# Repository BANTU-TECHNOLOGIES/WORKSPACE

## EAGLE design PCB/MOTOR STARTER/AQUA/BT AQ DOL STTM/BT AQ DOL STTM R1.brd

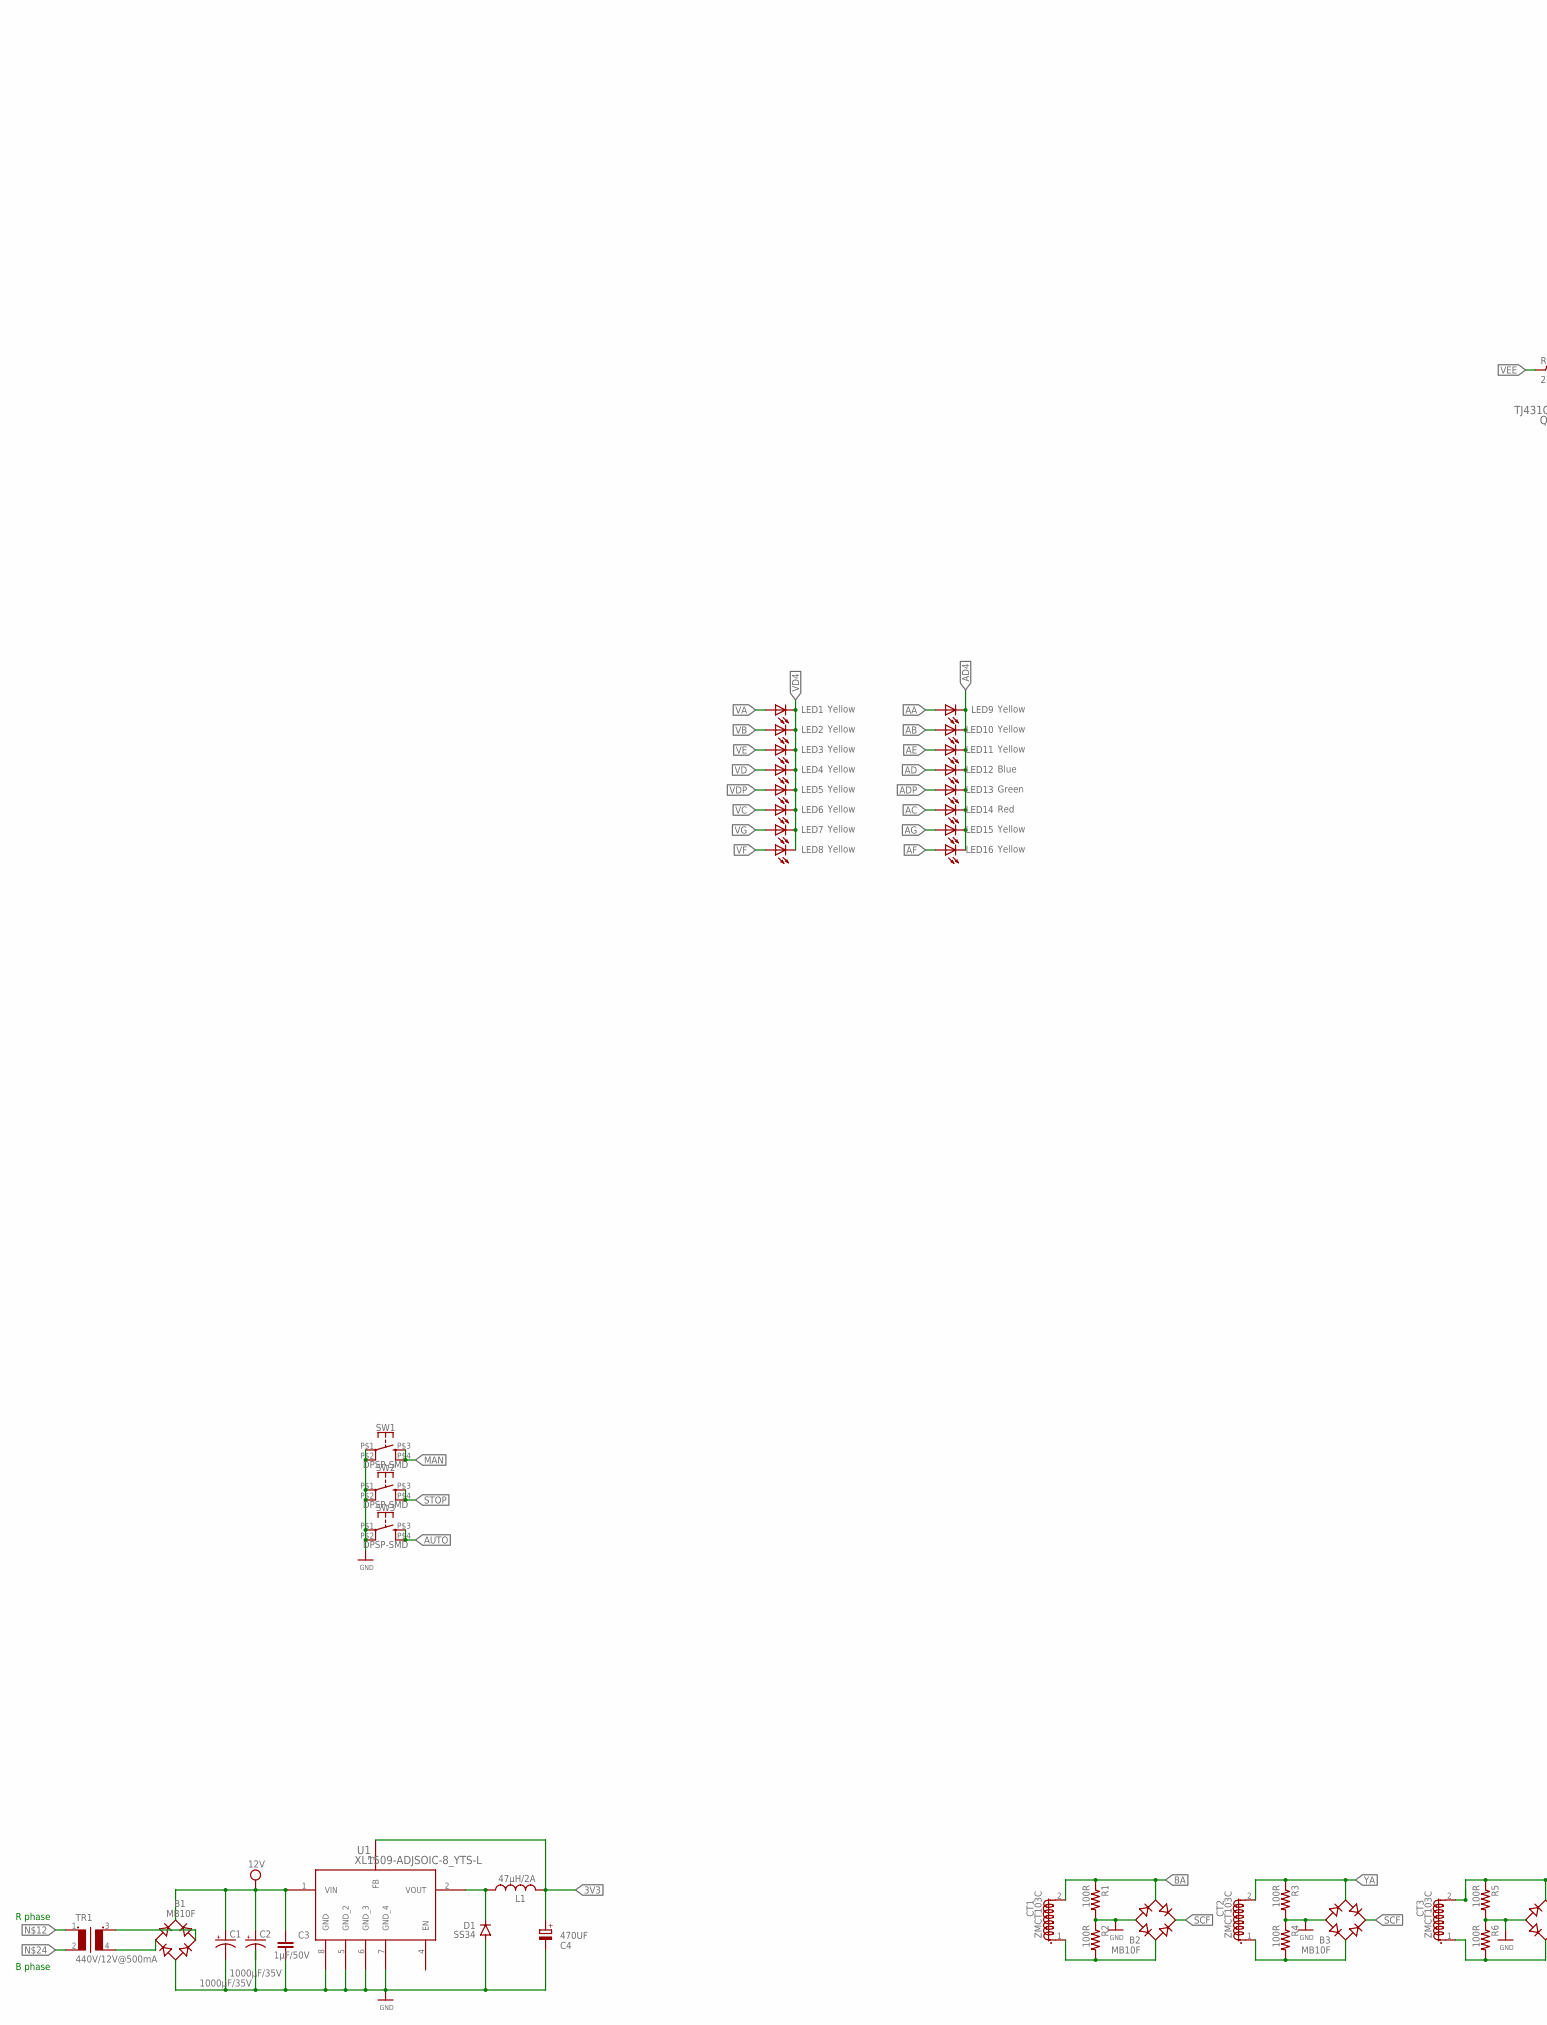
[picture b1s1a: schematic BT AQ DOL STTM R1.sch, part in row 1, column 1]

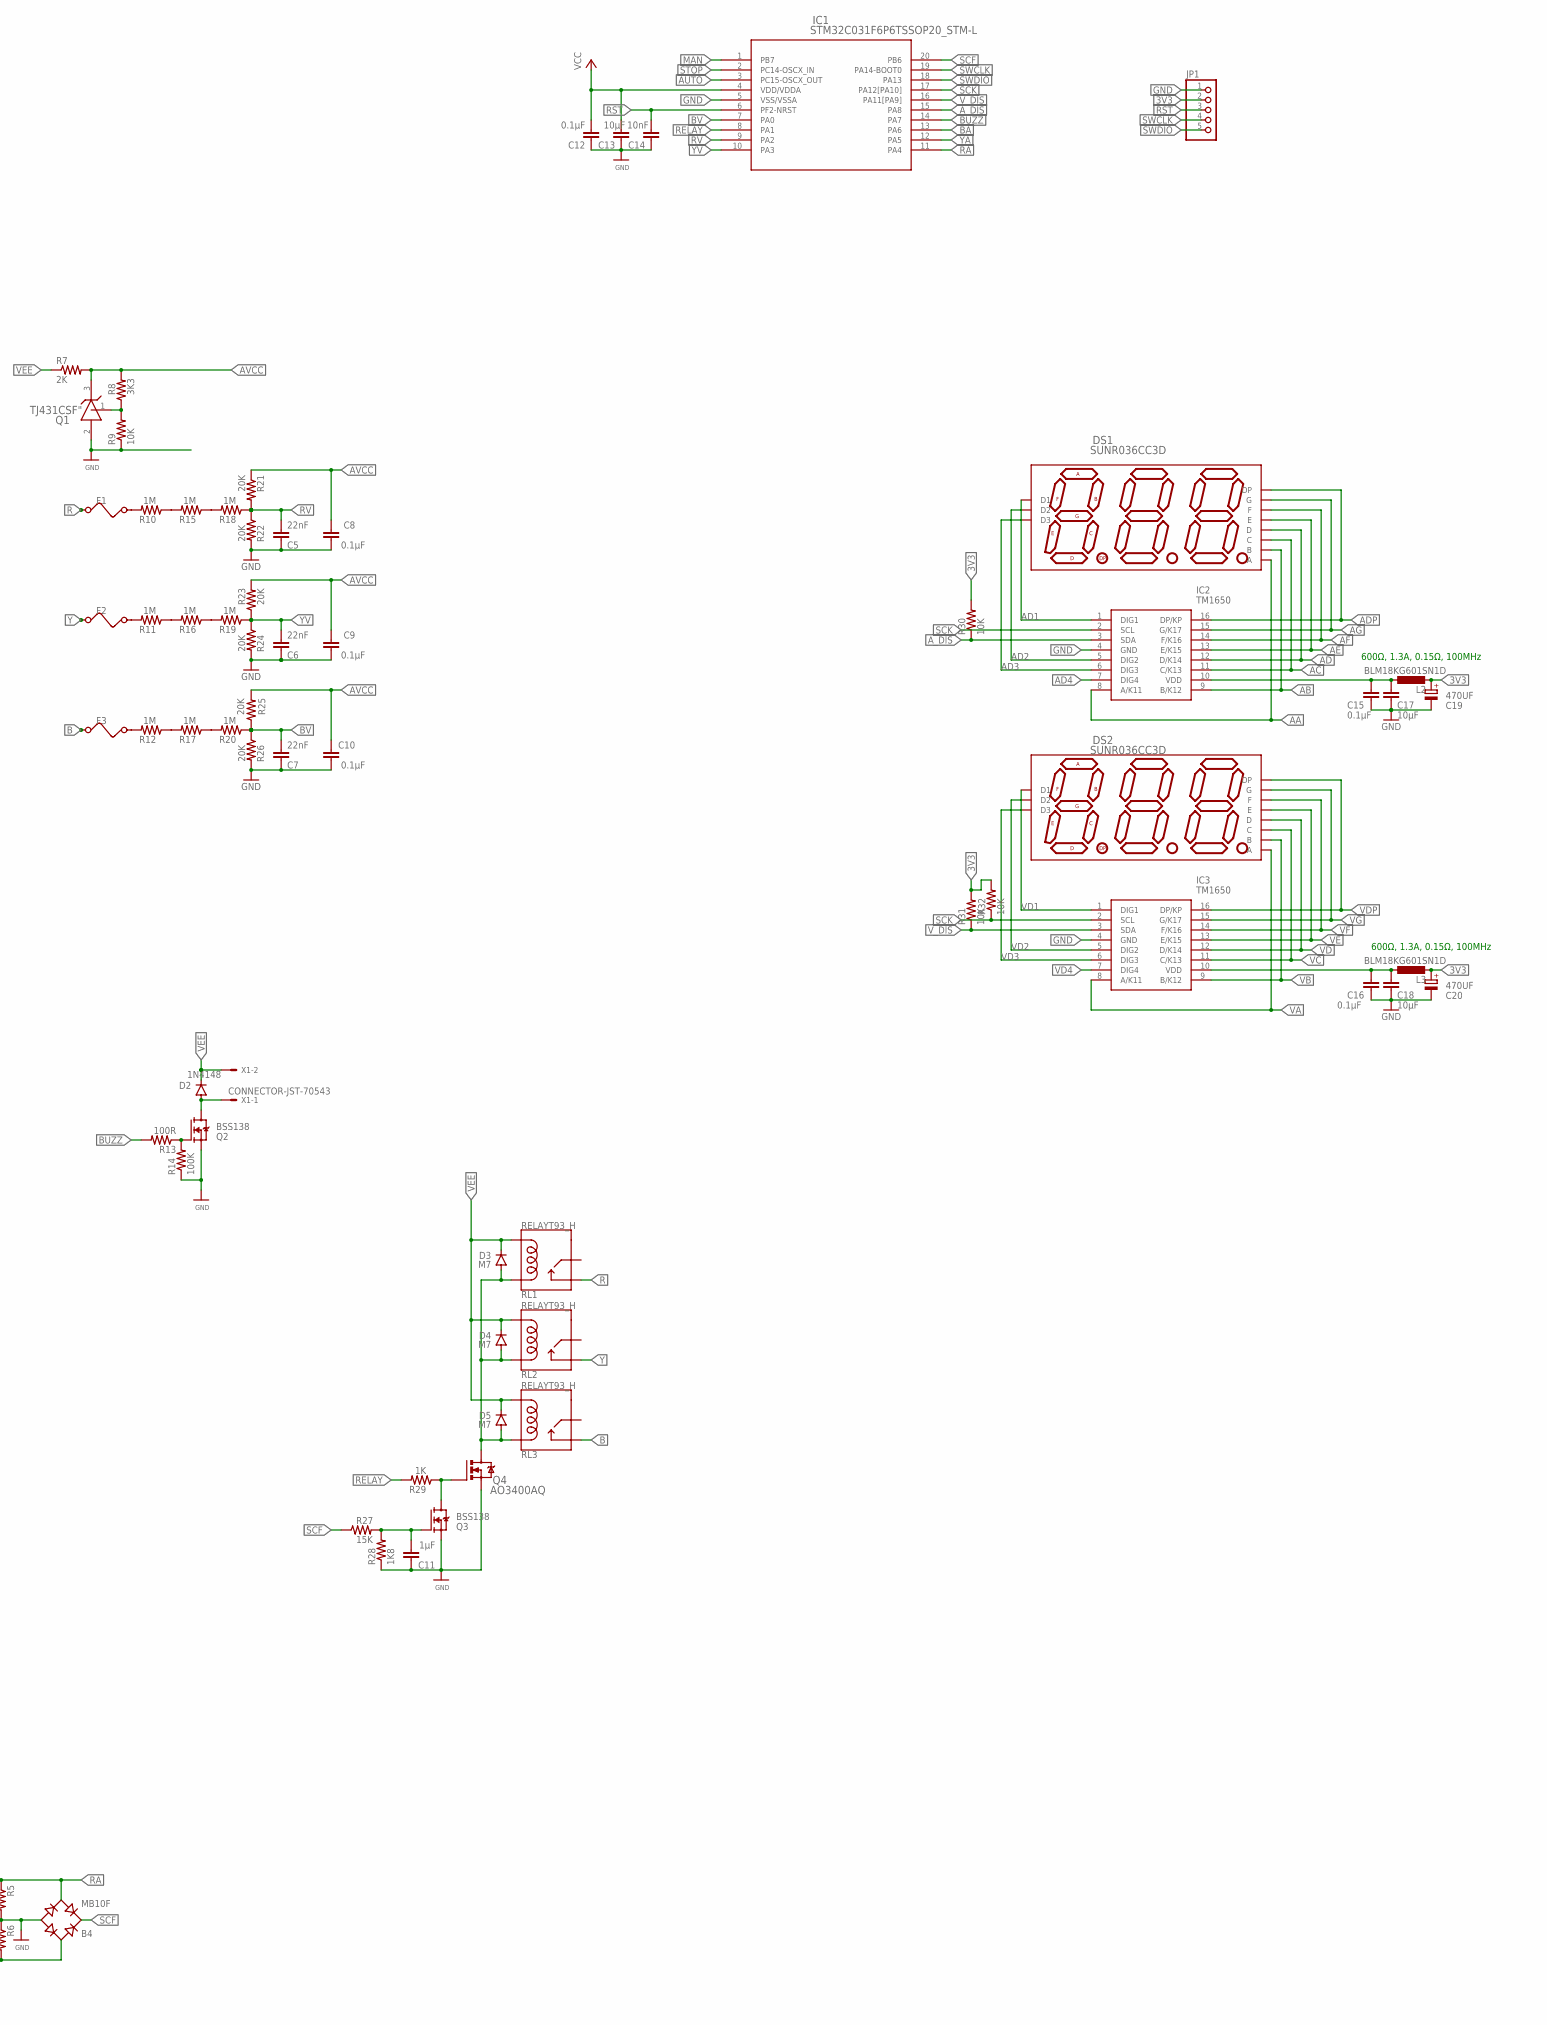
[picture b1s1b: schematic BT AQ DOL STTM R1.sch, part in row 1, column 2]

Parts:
B1, B2, B3, B4: MB10F; SOIC-4
C1, C2: 1000μF/35V; E5-13
C3: 1μF/50V; C0603K
C4, C19, C20: 470UF; E3,5-8
C5, C6, C7: 22nF; C1206
C8, C9, C10: 0.1μF; C1206
C11: 1μF; C1206
C12, C15, C16: 0.1μF; C0603K
C13, C17, C18: 10μF; C0805K
C14: 10nF; C1206
CT1, CT2, CT3: ZMCT103C
D1: SS34; DO214AC
D2: 1N4148; MINIMELF
D3, D4, D5: M7; DO214AC
DS1, DS2: SUNR036CC3D; 7S3D036_DIP
F1, F2, F3: FUSESMD; WIRE_FUSE
IC1: STM32C031F6P6TSSOP20_STM-L; TSSOP20_STM-L
IC2, IC3: TM1650; SOIC127P604X185-16N
JP1: PINHD-1X5; 1X05
L1: 47μH/2A; L5650M
L2, L3: BLM18KG601SN1D; L2012C
LED1, LED2, LED3, LED4, LED5, LED6, LED7, LED8, LED9, LED10, LED11, LED15, LED16: Yellow; LED3MM
LED12: Blue; LED3MM
LED13: Green; LED3MM
LED14: Red; LED3MM
Q1: TJ431CSF"; SOT-23
Q2, Q3: BSS138; SOT95P240X111-3N
Q4: AO3400AQ; SOT-23-DSG
R1, R2, R3, R4, R5, R6, R13: 100R; M1206
R7: 2K; M1206
R8: 3K3; M1206
R9, R30, R31, R32: 10K; M1206
R10, R11, R12, R15, R16, R17, R18, R19, R20: 1M; M1206
R14: 100K; M1206
R21, R22, R23, R24, R25, R26: 20K; M1206
R27: 15K; M1206
R28: 1K8; M1206
R29: 1K; M1206
RL1, RL2, RL3: RELAYT93_H; T93_H
SW1, SW2, SW3: DPSP-SMD; B3F-40XX-ROUND-SMD
TR1: 440V/12V@500mA; 440V12V6VA
U1: XL1509-ADJSOIC-8_YTS-L; SOIC-8_YTS-L
X1: CONNECTOR-JST-70543; 70543-02

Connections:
3V3: C4.+, C12.2, C13.2, C19.+, C20.+, IC1.4 (VDD/VDDA), JP1.2, L1.2, L2.2, L3.2, R30.2, R31.2, R32.2, U1.3 (FB)
AA: DS1.11 (A), IC2.8 (A/K11), LED9.A
AB: DS1.7 (B), IC2.9 (B/K12), LED10.A
AC: DS1.4 (C), IC2.11 (C/K13), LED14.A
AD: DS1.2 (D), IC2.12 (D/K14), LED12.A
AD1: DS1.12 (D1), IC2.1 (DIG1)
AD2: DS1.9 (D2), IC2.5 (DIG2)
AD3: DS1.8 (D3), IC2.6 (DIG3)
AD4: IC2.7 (DIG4), LED9.K (C), LED10.K (C), LED11.K (C), LED12.K (C), LED13.K (C), LED14.K (C), LED15.K (C), LED16.K (C)
ADP: DS1.3 (DP), IC2.16 (DP/KP), LED13.A
AE: DS1.1 (E), IC2.13 (E/K15), LED11.A
AF: DS1.10 (F), IC2.14 (F/K16), LED16.A
AG: DS1.5 (G), IC2.15 (G/K17), LED15.A
AUTO: IC1.3 (PC15-OSCX_OUT), SW3.P$3 (3), SW3.P$4 (4)
AVCC: C8.2, C9.2, C10.2, Q1.3 (CATHODE), R7.2, R8.2, R21.1, R23.2, R25.2
A_DIS: IC1.15 (PA8), IC2.3 (SDA), R30.1
B: F3.1, RL3.14 (N0)
BA: B2.~2 (AC2), CT1.2 (S1.2), IC1.13 (PA6), R1.1
BUZZ: IC1.14 (PA7), R13.2
BV: C7.2, IC1.7 (PA0), R20.1, R25.1, R26.1
GND: B1.-, B2.-, B3.-, B4.-, C1.-, C2.-, C3.1, C4.-, C5.1, C6.1, C7.1, C8.1, C9.1, C10.1, C11.1, C12.1, C13.1, C14.2, C15.1, C16.1, C17.1, C18.1, C19.-, C20.-, D1.A, IC1.5 (VSS/VSSA), IC2.4 (GND), IC3.4 (GND), JP1.1, Q1.2 (ANODE), Q2.2 (S), Q3.2 (S), Q4.S, R1.2, R2.1, R3.2, R4.1, R5.2, R6.1, R9.1, R14.1, R22.2, R24.2, R26.2, R28.1, SW1.P$1 (1), SW1.P$2 (2), SW2.P$1 (1), SW2.P$2 (2), SW3.P$1 (1), SW3.P$2 (2), U1.5 (GND_2), U1.6 (GND_3), U1.7 (GND_4), U1.8 (GND)
MAN: IC1.1 (PB7), SW1.P$3 (3), SW1.P$4 (4)
unnamed: R15.1, R18.2
unnamed: B1.~1 (AC1), TR1.4 (S2)
unnamed: C15.2, C17.2, IC2.10 (VDD), L2.1
unnamed: Q2.1 (G), R13.1, R14.2
unnamed: R17.1, R20.2
unnamed: Q3.3 (D), Q4.G, R29.1
unnamed: C16.2, C18.2, IC3.10 (VDD), L3.1
unnamed: D2.A, Q2.3 (D), X1.1
unnamed: B1.~2 (AC2), TR1.3 (S1)
unnamed: R10.1, R15.2
unnamed: F1.2, R10.2, TR1.1
unnamed: R11.1, R16.2
unnamed: R12.1, R17.2
unnamed: B2.~1 (AC1), CT1.1 (S1.1), R2.2
unnamed: D3.A, D4.A, D5.A, Q4.D, RL1.A1 (COIL1), RL2.A1 (COIL1), RL3.A1 (COIL1)
unnamed: R16.1, R19.2
unnamed: D1.C, L1.1, U1.2 (VOUT)
unnamed: Q1.1 (REF), R8.1, R9.2
unnamed: F2.2, R11.2
unnamed: F3.2, R12.2, TR1.2
unnamed: C11.2, Q3.1 (G), R27.2, R28.2
unnamed: B3.~1 (AC1), CT2.1 (S1.1), R4.2
unnamed: B4.~1 (AC1), CT3.1 (S1.1), R6.2
R: F1.1, RL1.14 (N0)
RA: B4.~2 (AC2), CT3.2 (S1.2), IC1.11 (PA4), R5.1
RELAY: IC1.8 (PA1), R29.2
RST: C14.1, IC1.6 (PF2-NRST), JP1.3
RV: C5.2, IC1.9 (PA2), R18.1, R21.2, R22.1
SCF: B2.+, B3.+, B4.+, IC1.20 (PB6), R27.1
SCK: IC1.17 (PA12[PA10]), IC2.2 (SCL), IC3.2 (SCL), R32.1
STOP: IC1.2 (PC14-OSCX_IN), SW2.P$3 (3), SW2.P$4 (4)
SWCLK: IC1.19 (PA14-BOOT0), JP1.4
SWDIO: IC1.18 (PA13), JP1.5
VA: DS2.11 (A), IC3.8 (A/K11), LED1.A
VB: DS2.7 (B), IC3.9 (B/K12), LED2.A
VC: DS2.4 (C), IC3.11 (C/K13), LED6.A
VD: DS2.2 (D), IC3.12 (D/K14), LED4.A
VD1: DS2.12 (D1), IC3.1 (DIG1)
VD2: DS2.9 (D2), IC3.5 (DIG2)
VD3: DS2.8 (D3), IC3.6 (DIG3)
VD4: IC3.7 (DIG4), LED1.K (C), LED2.K (C), LED3.K (C), LED4.K (C), LED5.K (C), LED6.K (C), LED7.K (C), LED8.K (C)
VDP: DS2.3 (DP), IC3.16 (DP/KP), LED5.A
VE: DS2.1 (E), IC3.13 (E/K15), LED3.A
VEE: B1.+, C1.+, C2.+, C3.2, D2.C, D3.C, D4.C, D5.C, R7.1, RL1.A2 (COIL2), RL2.A2 (COIL2), RL3.A2 (COIL2), U1.1 (VIN), X1.2
VF: DS2.10 (F), IC3.14 (F/K16), LED8.A
VG: DS2.5 (G), IC3.15 (G/K17), LED7.A
V_DIS: IC1.16 (PA11[PA9]), IC3.3 (SDA), R31.1
Y: F2.1, RL2.14 (N0)
YA: B3.~2 (AC2), CT2.2 (S1.2), IC1.12 (PA5), R3.1
YV: C6.2, IC1.10 (PA3), R19.1, R23.1, R24.1

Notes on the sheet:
R phase
B phase
600Ω, 1.3A, 0.15Ω, 100MHz

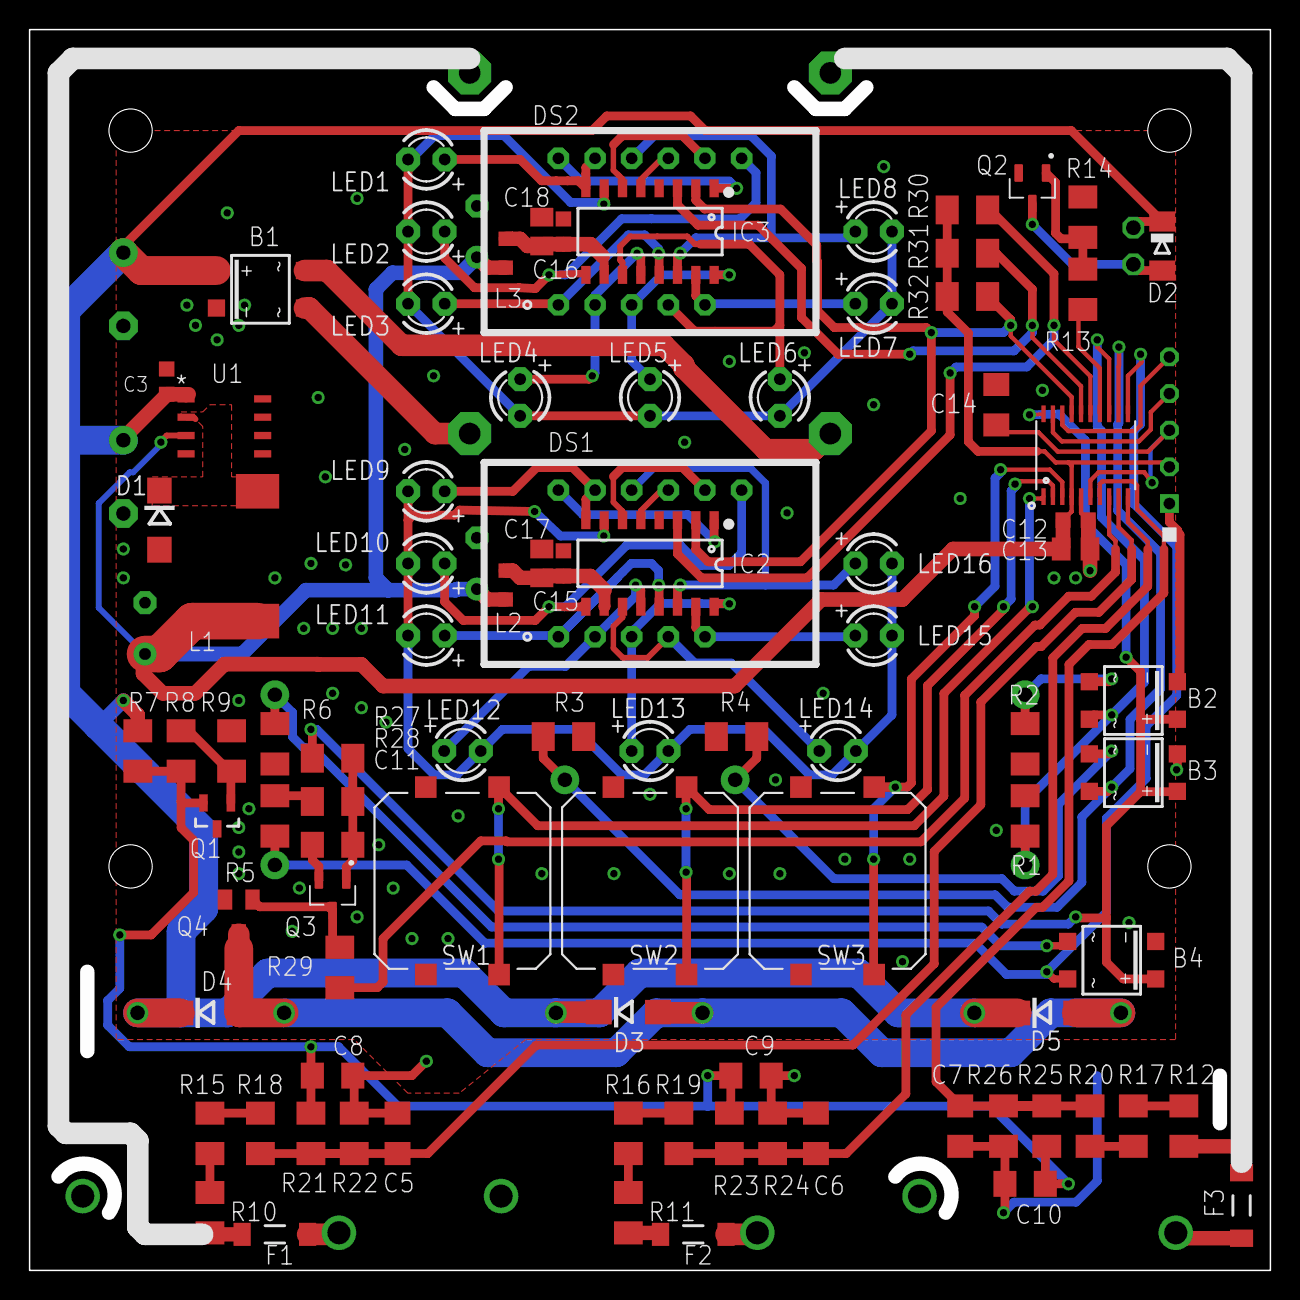
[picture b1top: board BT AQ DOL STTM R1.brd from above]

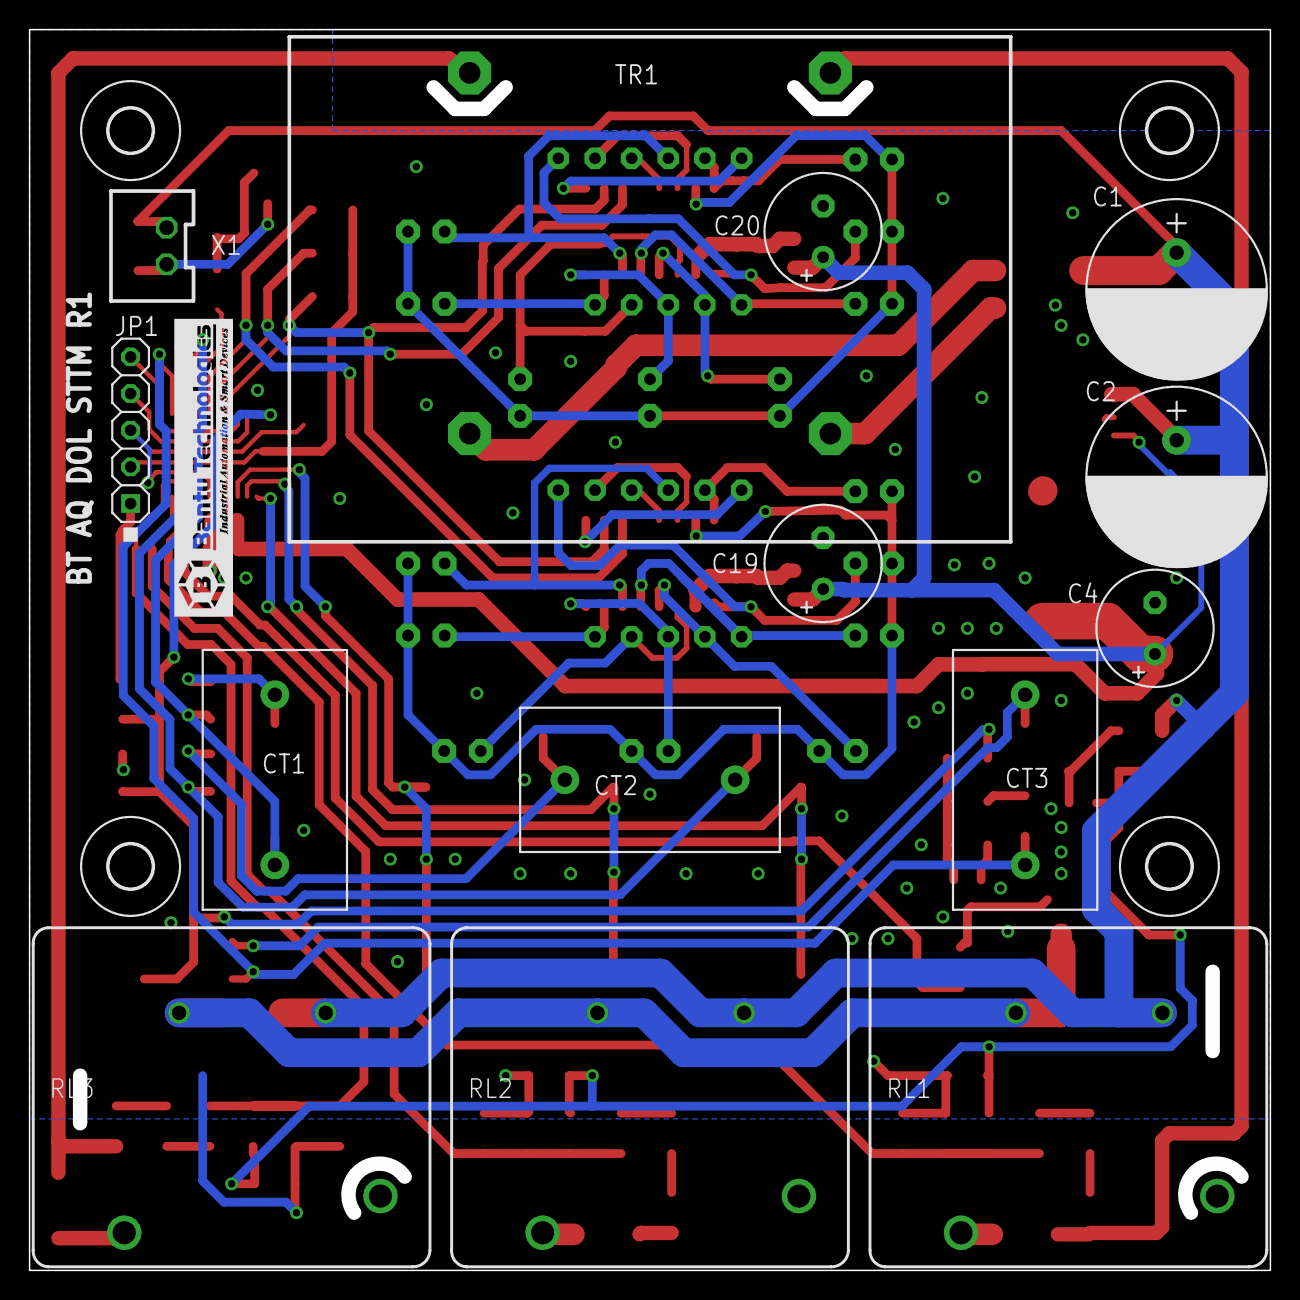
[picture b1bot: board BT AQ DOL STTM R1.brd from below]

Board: 2 copper layers, 86.0 x 86.0 mm, 109 parts (18 on the bottom side), 72 nets.

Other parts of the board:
U$5, U$6, U$17, U$29: 3,0

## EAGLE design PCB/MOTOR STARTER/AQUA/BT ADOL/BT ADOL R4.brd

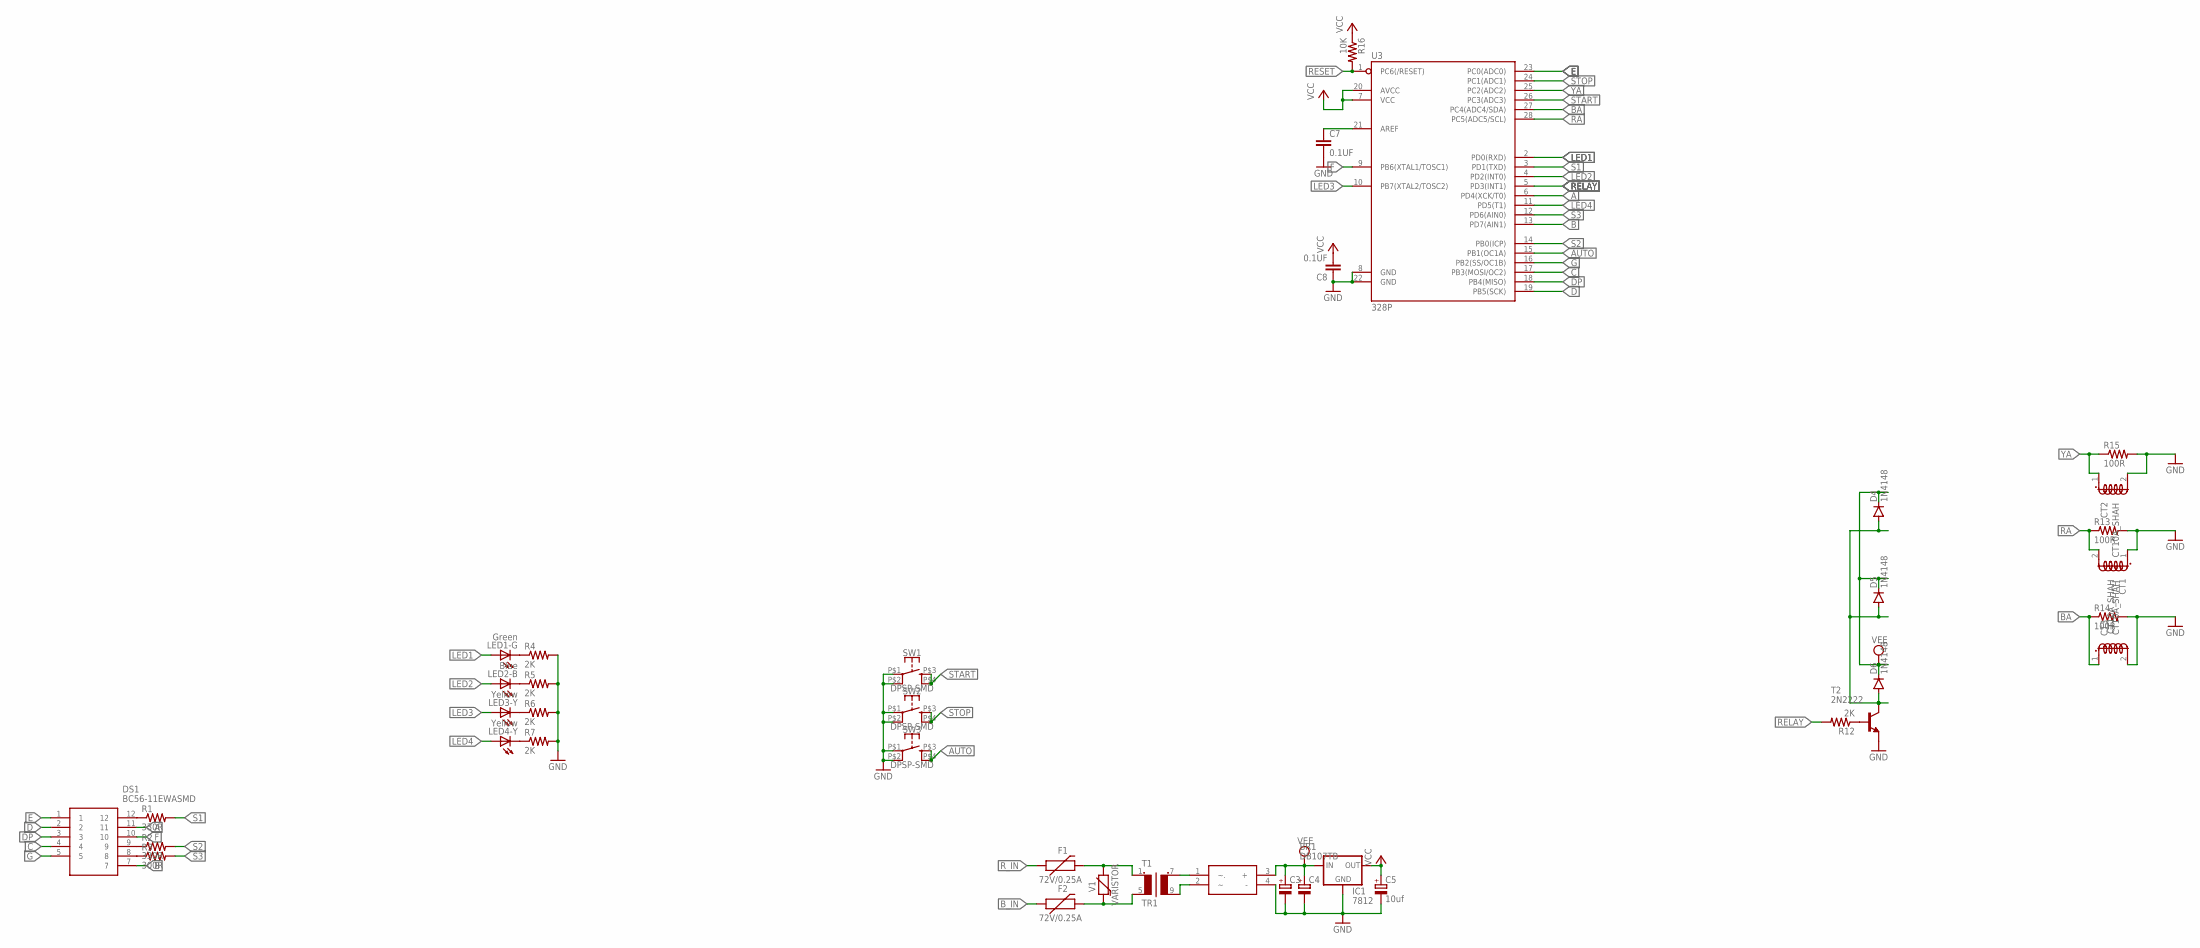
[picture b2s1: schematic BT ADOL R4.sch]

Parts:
BR1: DB107TB; DIP845W60P510L815H400Q4N
C3, C4: CPOL-EUE3.5-10; E3,5-10
C5: 10uf; E2-4
C7, C8: 0.1UF; C1206
CT1, CT2, CT3: CT10A_SHAH; 10A_SHAH
D4, D5, D6: 1N4148; MINIMELF
DS1: BC56-11EWASMD; 7SEGMENT-SMD
F1, F2: 72V/0.25A; PTH
IC1: 7812; 78XXS
LED1-G: Green; LED3MM
LED2-B: Blue; LED3MM
LED3-Y, LED4-Y: Yellow; LED3MM
R1, R2: 330R; R1206
R3: 300R; R1206
R4, R5, R6, R7: 2K; R1206
R12: 2K; M1206
R13, R14, R15: 100R; M1206
R16: 10K; M1206
SW1, SW2, SW3: DPSP-SMD; B3F-40XX-ROUND-SMD
T1: TR1; 44022012
T2: 2N2222; TO92-EBC-OVAL
U3: 328P; DIP28
V1: VARISTOR; 10MM

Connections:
A: DS1.11, U3.6 (PD4(XCK/T0))
AUTO: SW3.P$3 (3), SW3.P$4 (4), U3.15 (PB1(OC1A))
B: DS1.7, U3.13 (PD7(AIN1))
BA: CT3.1 (S1.1), R14.1, U3.27 (PC4(ADC4/SDA))
B_IN: F2.P$1 (1)
C: DS1.4, U3.17 (PB3(MOSI/OC2))
D: DS1.2, U3.19 (PB5(SCK))
DP: DS1.3, U3.18 (PB4(MISO))
E: DS1.1, U3.23 (PC0(ADC0))
F: DS1.10, U3.9 (PB6(XTAL1/TOSC1))
G: DS1.5, U3.16 (PB2(SS/OC1B))
GND: BR1.4 (-), C3.-, C4.-, C5.-, C7.2, C8.1, CT1.1 (S1.1), CT2.2 (S1.2), CT3.2 (S1.2), IC1.GND, R4.2, R5.2, R6.2, R7.2, R13.2, R14.2, R15.2, SW1.P$1 (1), SW1.P$2 (2), SW2.P$1 (1), SW2.P$2 (2), SW3.P$1 (1), SW3.P$2 (2), T2.E, U3.8 (GND), U3.22 (GND)
LED1: LED1-G.A, U3.2 (PD0(RXD))
LED2: LED2-B.A, U3.4 (PD2(INT0))
LED3: LED3-Y.A, U3.10 (PB7(XTAL2/TOSC2))
LED4: LED4-Y.A, U3.11 (PD5(T1))
unnamed: LED1-G.K (C), R4.1
unnamed: BR1.2, T1.9 (S2)
unnamed: LED2-B.K (C), R5.1
unnamed: LED3-Y.K (C), R6.1
unnamed: R12.1, T2.B
unnamed: D4.A, D5.A, D6.A, T2.C
unnamed: BR1.1 (~.), T1.7 (S1)
unnamed: DS1.12, R1.1
unnamed: DS1.9, R2.1
unnamed: DS1.8, R3.1
unnamed: F1.P$2 (2), T1.1, V1.2
unnamed: LED4-Y.K (C), R7.1
unnamed: F2.P$2 (2), T1.5 (P2), V1.1
unnamed: C7.1, U3.21 (AREF)
RA: CT1.2 (S1.2), R13.1, U3.28 (PC5(ADC5/SCL))
RELAY: R12.2, U3.5 (PD3(INT1))
RESET: R16.2, U3.1 (PC6(/RESET))
R_IN: F1.P$1 (1)
S1: R1.2, U3.3 (PD1(TXD))
S2: R2.2, U3.14 (PB0(ICP))
S3: R3.2, U3.12 (PD6(AIN0))
START: SW1.P$3 (3), SW1.P$4 (4), U3.26 (PC3(ADC3))
STOP: SW2.P$3 (3), SW2.P$4 (4), U3.24 (PC1(ADC1))
VCC: C5.+, C8.2, IC1.OUT, R16.1, U3.7 (VCC), U3.20 (AVCC)
VEE: BR1.3 (+), C3.+, C4.+, D4.C, D5.C, D6.C, IC1.IN
YA: CT2.1 (S1.1), R15.1, U3.25 (PC2(ADC2))

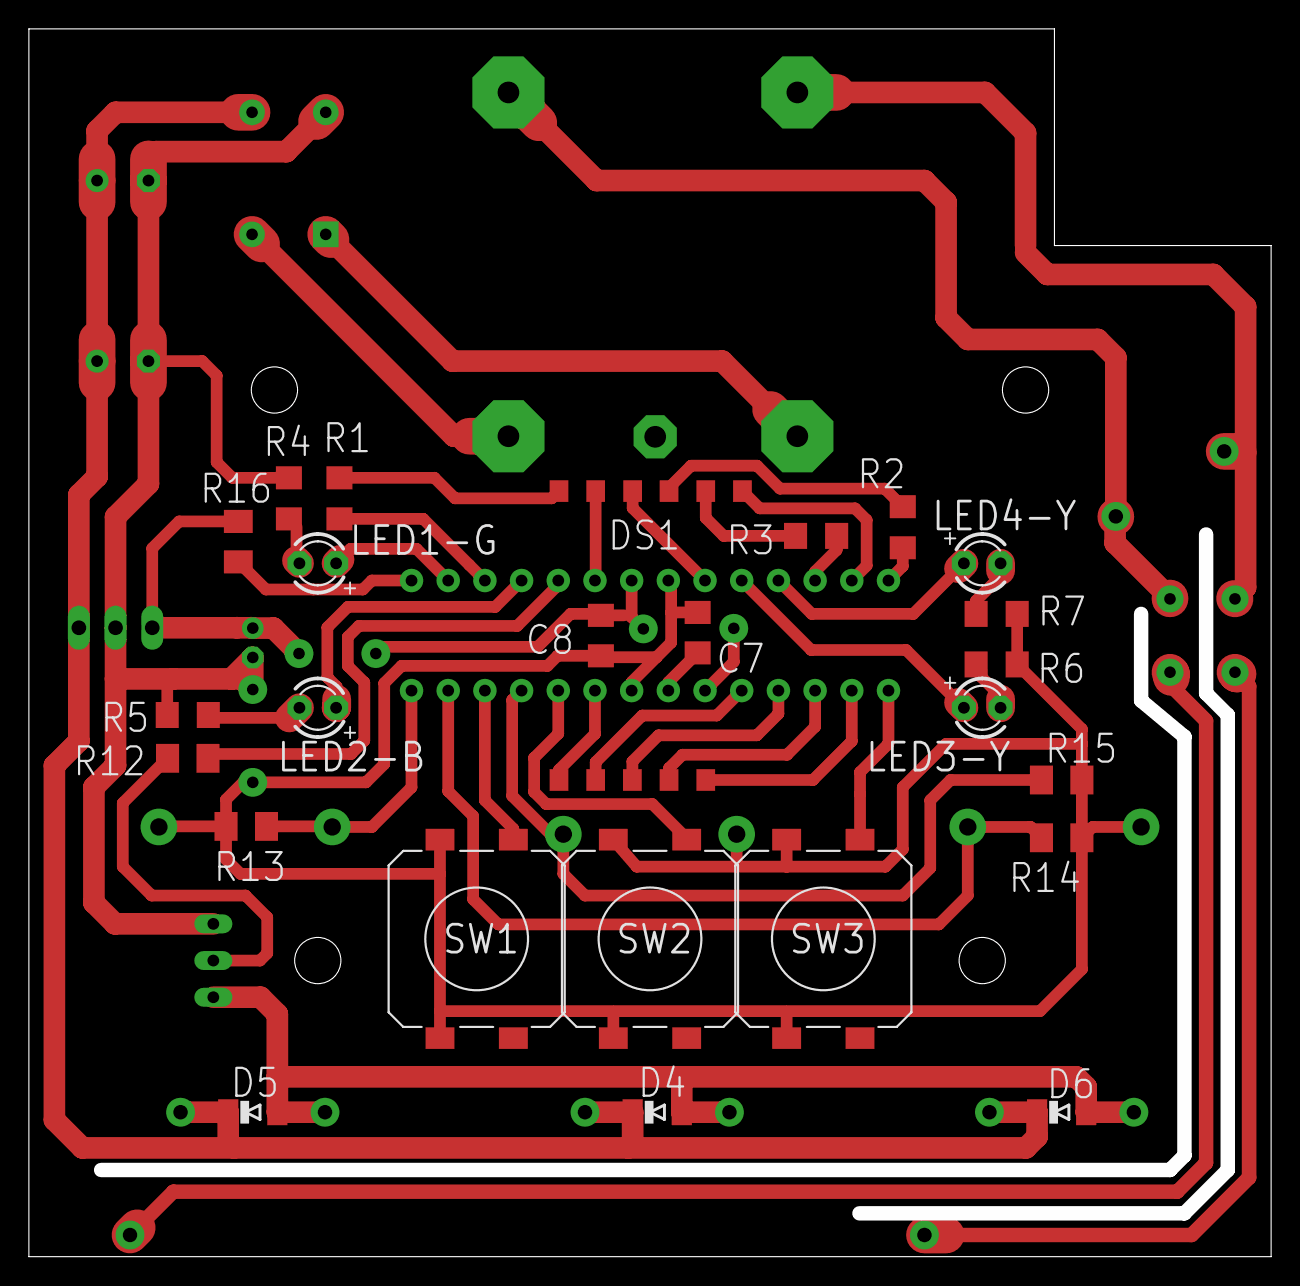
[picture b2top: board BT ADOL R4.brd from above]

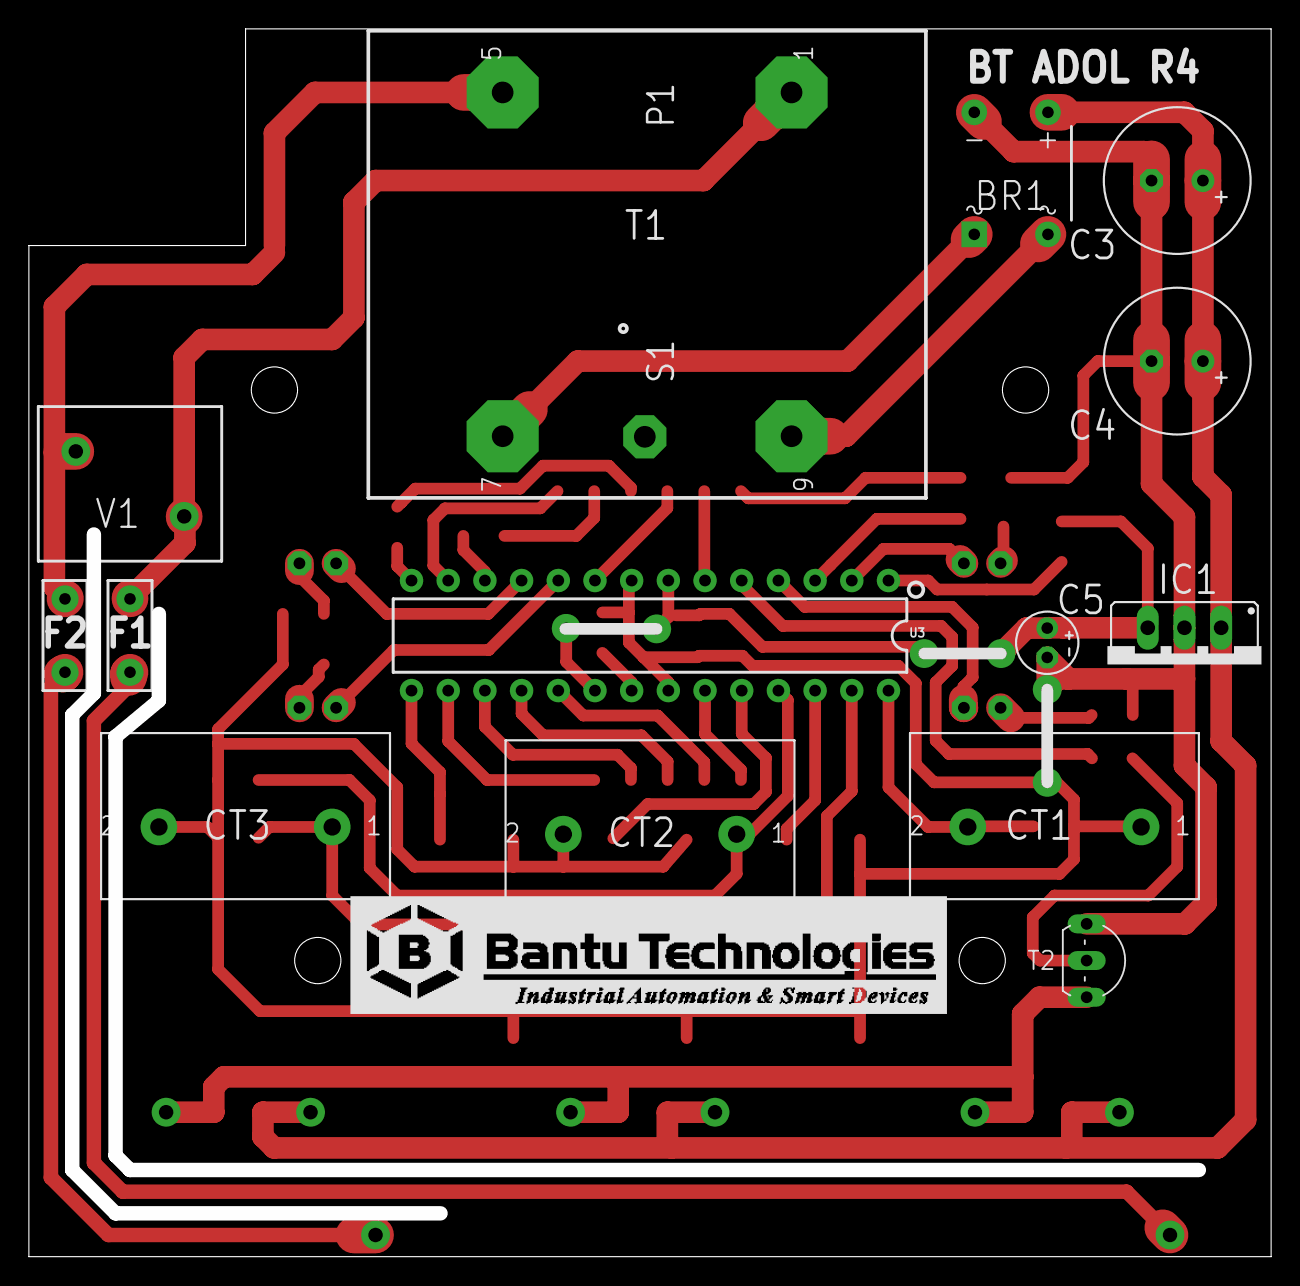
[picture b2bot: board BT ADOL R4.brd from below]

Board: 2 copper layers, 86.0 x 85.0 mm, 39 parts (14 on the bottom side), 40 nets.

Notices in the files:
parts and their libraries:
SparkFun-Fuses: Licensing: Creative Commons ShareAlike 4.0 International - https://creativecommons.org/licenses/by-sa/4.0
COPYRIGHT: Copyright (C) 2024 Ultra Librarian. All rights reserved.
COPYRIGHT: Copyright (C) 2026 Ultra Librarian. All rights reserved.
